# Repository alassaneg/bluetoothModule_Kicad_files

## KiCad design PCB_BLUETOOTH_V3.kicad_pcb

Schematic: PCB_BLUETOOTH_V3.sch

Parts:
C1, C9: 4,7uF; C_0805_2012Metric_Pad1.15x1.40mm_HandSolder; Manufacturer_Part_Number GRM21BR61H475KE51L; Farnell Part Number 2611942
C2, C3: 10uF; C_0805_2012Metric_Pad1.15x1.40mm_HandSolder; Manufacturer_Part_Number 08051A330JAT2A; Farnell Part Number 317603
C4, C7, C14, C15, C16, C17, C21, C22: 100nF; C_0603_1608Metric_Pad1.05x0.95mm_HandSolder; Manufacturer_Part_Number 06033D104KAT2A; Farnell Part Number 2332591
C8, C20: 10uF; C_0805_2012Metric_Pad1.15x1.40mm_HandSolder; Manufacturer_Part_Number C0805C106K3PACTU; Farnell Part Number 2491176
C11: 470nF; C_0603_1608Metric_Pad1.05x0.95mm_HandSolder; Manufacturer_Part_Number GRM033R60J474KE90D; Farnell Part Number 2990686
C12, C13, C19, C24, C27, C28, C30, C32: 1uF; C_0603_1608Metric_Pad1.05x0.95mm_HandSolder; Manufacturer_Part_Number 06033D105KAT2A; Farnell Part Number 1658868
C18, C26: 33pF; C_0805_2012Metric_Pad1.15x1.40mm_HandSolder; Manufacturer_Part_Number 08051A330JAT2A; Farnell Part Number 317603
C23, C25, C29, C31: 15pF; C_0805_2012Metric_Pad1.15x1.40mm_HandSolder; Manufacturer_Part_Number 08051A150JAT2A; Farnell Part Number 1658873
D1, D2, D3, D4, D9, D12, D13, D14: KPTR-3216SURCK; LED_0805_2012Metric_Pad1.15x1.40mm_HandSolder; Manufacturer_Part_Number KPTR-3216SURCK; Farnell Part Number 2099256
D5: DIODE; D_SOD-123; Manufacturer_Part_Number SBR1A40S1; Farnell Part Number 2061529
D6, D7: MAX40203AUK+T; SOT95P280X145-5N; Manufacturer_Part_Number MAX40203AUK+T; Mouser Part Number 700-MAX40203AUK+T
D8: ESD5B_ESD; D_SOD-323_HandSoldering; Manufacturer_Part_Number ESD5B5.0ST1G; Farnell Part Number 2317513
D11: KPT-1608EC; LED_0603_1608Metric_Pad1.05x0.95mm_HandSolder; Manufacturer_Part_Number KPTR-3216SURCK; Farnell Part Number 2099256
DS1: KCDA39-105; KCDA39105; Manufacturer_Part_Number KPT-1608EC; Mouser Part Number N/A
IC2: PIC18F46J50-I_PT; QFP80P1200X1200X120-44N; Manufacturer_Part_Number PIC18F46J50-I/PT; Mouser Part Number 579-PIC18F46J50-I/PT
IC3, IC4: SIP32431DR3-T1GE3; SOT65P210X110-6N; Manufacturer_Part_Number SIP32431DR3-T1GE3; Mouser Part Number 781-SIP32431DR3-GE3
IC6: MAX17263LETD+; SON40P300X300X80-15N; Manufacturer_Part_Number MAX17263LETD+; Mouser Part Number 700-MAX17263LETD+
IC7: WT32i-A-AI6; WT32I-A-AI6; Manufacturer_Part_Number WT32i-A-AI6; Mouser Part Number 603-WT32I-A-AI6
IC8: AD8476ARMZ; SOP65P490X110-8N; Manufacturer_Part_Number AD8476ARMZ; Mouser Part Number 584-AD8476ARMZ
J1: UART; PinSocket_1x04_P2.54mm_Vertical
J2: CL1308G; Manufacturer_Part_Number CL1308G; Farnell Part Number 2766190
J3: PJRAS1X2S01X; Mouser Part Number 502-PJRAS1X2S01X
J4: SP-3533-02; SP353302; Manufacturer_Part_Number SP-3533-02; Mouser Part Number 490-SP-3533-02
J5: 22-03-5035; SHDR3W70P0X250_1X3_990X490X590P; Manufacturer_Part_Number 22-03-5035; Mouser Part Number 538-22-03-5035
J6: ICSP_UC; PinSocket_1x05_P2.54mm_Vertical
J8: USB_B_Micro; DX4R005HJ5
J9: SPI_WT32i; PinSocket_1x06_P2.54mm_Vertical
JP1: Jumper_AUDIO_ROUTING; PinHeader_1x03_P2.54mm_Vertical; Manufacturer_Part_Number 22-28-4031; Farnell Part Number 3049527
JP2: Jumper_MONO_STEREO; PinHeader_1x03_P2.54mm_Vertical; Manufacturer_Part_Number 22-28-4031; Farnell Part Number 3049527
JP3: Jumper_NO_Small; PinHeader_1x02_P2.54mm_Vertical
JP4: Jumper_ICSP; PinHeader_1x02_P2.54mm_Vertical; Manufacturer_Part_Number 90120-0762; Farnell Part Number 9733302
JP5: JP_UART_RX; PinHeader_1x02_P2.54mm_Vertical; Manufacturer_Part_Number 90120-0762; Farnell Part Number 9733302
JP8: JP_UART_TX; PinHeader_1x02_P2.54mm_Vertical; Manufacturer_Part_Number 90120-0762; Farnell Part Number 9733302
L1, L4: 33nH; L_0805_2012Metric_Pad1.15x1.40mm_HandSolder; Manufacturer_Part_Number CE201210-33NJ; Farnell Part Number 2858904
L2, L3, L5, L6: 15nH; L_0603_1608Metric_Pad1.05x0.95mm_HandSolder; Manufacturer_Part_Number CE201210-15NJ; Farnell Part Number 2858903
Q1, Q2, Q3, Q4, Q5, Q6, Q7: 2SC4102FRAT106; RYU002N05T306; Manufacturer_Part_Number 2SC4102FRAT106
R1, R2: 1000kOhm; R_0805_2012Metric_Pad1.15x1.40mm_HandSolder; Manufacturer_Part_Number CRCW08050000Z0EA; Farnell Part Number 1469846
R5: 10M; R_0805_2012Metric_Pad1.15x1.40mm_HandSolder; Manufacturer_Part_Number CRCW080510M0FKEA; Farnell Part Number 1469858
R6, R7, R8, R9: 1.6kOhm; R_0805_2012Metric_Pad1.15x1.40mm_HandSolder; Manufacturer_Part_Number ERJ6ENF2150V; Farnell Part Number 2303478
R10, R14, R17: 2,2k; R_0805_2012Metric_Pad1.15x1.40mm_HandSolder; Manufacturer_Part_Number CRCW08052K20FKEA; Farnell Part Number 1469887
R11, R12, R13, R16: 7,5k; R_0805_2012Metric_Pad1.15x1.40mm_HandSolder; Manufacturer_Part_Number CRCW08057K50FKEA; Farnell Part Number 1653036
R15: 1.74kOhm; R_0805_2012Metric_Pad1.15x1.40mm_HandSolder; Manufacturer_Part_Number CRCW0805120RFKEA; Farnell Part Number 1652914
R18: 402ohm; L_0603_1608Metric_Pad1.05x0.95mm_HandSolder; Manufacturer_Part_Number ERA6AEB4020V; Farnell Part Number 1810462
R19, R39, R40: 5.1k; R_0805_2012Metric_Pad1.15x1.40mm_HandSolder; Manufacturer_Part_Number CRCW08055K00FKTA; Farnell Part Number 2616759
R20, R22, R24, R26, R27, R30, R31: 240k; R_0805_2012Metric_Pad1.15x1.40mm_HandSolder; Manufacturer_Part_Number ERJ6ENF4223V; Farnell Part Number 2303832
R21, R23, R25, R28, R29, R32, R33: 806ohm; R_0805_2012Metric_Pad1.15x1.40mm_HandSolder; Manufacturer_Part_Number ERJ6ENF6980V; Farnell Part Number 2303535
R34, R35, R36, R37: 10k; R_0805_2012Metric_Pad1.15x1.40mm_HandSolder; Manufacturer_Part_Number CPF-A-0805B10KE1; Farnell Part Number 2483951
R44, R45, R46, R47, R48, R49: 0ohm; R_0805_2012Metric_Pad1.15x1.40mm_HandSolder; Manufacturer_Part_Number CRCW08050000Z0EA; Farnell Part Number 1469846
R52: 1.74kOhm; R_0805_2012Metric_Pad1.15x1.40mm_HandSolder; Manufacturer_Part_Number ERA6AEB4020V; Farnell Part Number 1810462
R53, R54, R55: 1.74kOhm; R_0402_1005Metric; Manufacturer_Part_Number CRCW0402120RFKED; Farnell Part Number 2140682
S1: 450302014072; Manufacturer_Part_Number 450302014072; Mouser Part Number 710-450302014072
S2: PT65301; Manufacturer_Part_Number PT65301; Mouser Part Number 642-PT65301
TP1, TP4: 3V3; TestPoint_Pad_D1.0mm
TP2: GND; TestPoint_Pad_D1.0mm
TP3: Clock; TestPoint_Pad_D1.0mm
TP7: DIG1_7seg; TestPoint_Pad_D1.0mm
TP8: DIG2_7seg; TestPoint_Pad_D1.0mm
U1: REG113NA-3.3_3K; Texas_Instruments-DBV0005A-0-0-IPC_A; dropout voltage 250mV; output voltage 3.3V; mouser part number 595-REG113NA-3.3/3K; digikey description IC REG LINEAR 3.3V 400MA SOT23-5
U2: OPA1671IDCKT; SOT65P210X110-5N; Manufacturer_Part_Number OPA1671IDCKT; Mouser Part Number 595-OPA1671IDCKT

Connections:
3V3: C7.1, C8.2, C9.1, C12.1, C13.1, C16.1, C21.2, C22.2, D9.2 (A), D13.2 (A), IC2.7 (VDD), IC2.28 (VDD_1), IC3.4 (IN), IC4.4 (IN), IC7.1 (VREG_ENA), IC7.17 (VDD_IO), IC8.2 (+VS), J6.4, J9.1, R1.1, R19.1, R34.1, R35.1, R39.1, R40.1, S2.C1, S2.C2, TP1.1, U1.5 (VOUT), U2.5 (V+)
/DIFF1+: L2.2, R10.1, R11.2
/DIFF1-: L3.2, R10.2, R13.2
/DIFF2+: C19.2, C23.1, L2.1
/DIFF2-: C24.2, C25.1, L3.1
/DIFF3+: C19.1, R44.2
/DIFF3-: C24.1, R46.2
AUDIO_DIFF_N: IC8.5 (-OUT), R13.1
AUDIO_DIFF_P: IC8.4 (+OUT), R11.1
AUDIO_IN_N_LEFT_N: IC7.45 (AUDIO_IN_N_LEFT), R46.1, R47.1
AUDIO_IN_N_RIGHT: C32.2, IC7.42 (AUDIO_IN_N_RIGHT_N)
AUDIO_IN_P_LEFT_P: IC7.44 (AUDIO_IN_P_LEFT), R44.1, R45.1
AUDIO_IN_P_RIGHT: C30.1, IC7.41 (AUDIO_IN_P_RIGHT_P)
AUDIO_MONO_STEREO: IC2.2 (RD4/PMD4/RP21), JP2.2 (C)
AUDIO_OUT_N_LEFT: IC7.49 (AUDIO_OUT_N_LEFT)
AUDIO_OUT_N_RIGHT: IC7.46 (AUDIO_OUT_N_RIGHT)
AUDIO_OUT_P_LEFT: C18.1, IC7.50 (AUDIO_OUT_P_LEFT), L1.1
AUDIO_OUT_P_LEFT_MONO: J3.T2, L1.2, R49.1
AUDIO_OUT_P_RIGHT: C26.1, IC7.47 (AUDIO_OUT_P_RIGHT), L4.1
AUDIO_ROUTING: IC2.3 (RD5/PMD5/RP22), JP1.2 (C)
AUDIO_SINGLE_ENDED_MONO: IC8.8 (INP), U2.1 (OUT), U2.4 (-IN)
A_7SEG: IC2.26 (RE1/AN6/PMWR), R20.2
BAT_TH: IC6.1 (TH), J5.2
B_7SEG: IC2.19 (RA0/AN0/C1INA/ULPWU/PMA6/RP0), R22.2
C_7SEG: IC2.21 (RA2/AN2/VREF-/CVREF-/C2INB), R24.2
DIG1: C15.1, DS1.10 (COM_A_DIG1), IC3.1 (OUT)
DIG1_7SEG: IC2.20 (RA1/AN1/C2INA/PMA7/RP1), IC3.3 (ON/OFF), TP7.1
DIG2: C14.1, DS1.5 (COMA_DIG2), IC4.1 (OUT)
DIG2_7SEG: IC2.24 (RA5/AN4/~SS1~/HLVDIN/RCV/RP2), IC4.3 (ON/OFF), TP8.1
D_7SEG: IC2.25 (RE0/AN5/PMRD), R27.2
E_7SEG: IC2.22 (RA3/AN3/VREF+/C1INB), R31.2
F_7SEG: IC2.27 (RE2/AN7/PMCS), R26.2
GND: C1.2, C3.1, C4.2, C7.2, C8.1, C9.2, C11.2, C12.2, C13.2, C14.2, C15.2, C16.2, C17.2, C18.2, C20.1, C21.1, C22.1, C23.2, C25.2, C26.2, C27.1, C29.2, C31.2, C32.1, D6.2 (GND), D7.2 (GND), D8.2 (A), D11.1 (K), D12.1 (K), D14.1 (K), IC2.6 (VSS), IC2.29 (VSS_1), IC3.2 (GND_1), IC3.5 (GND_2), IC4.2 (GND_1), IC4.5 (GND_2), IC6.8 (GND), IC6.9 (CSPL), IC6.12 (ALRT), IC6.15 (EP), IC7.2 (GND_1), IC7.3 (GND_2), IC7.4 (GND_3), IC7.18 (GND_4), IC7.21 (UART_NCTS), IC7.31 (GND_5), IC7.39 (GND_6), IC7.43 (GND_7), IC7.48 (GND_8), IC8.1 (INN), IC8.7 (-VS), J1.2, J2.3, J3.S1, J4.3 (SLEEVE), J5.3, J6.3, J8.5 (GND), J8.6 (Shield), J9.6, Q1.1, Q2.1, Q3.1, Q4.1, Q5.1, Q6.1, Q7.1, R2.2, R14.2, R17.2, R36.2, R37.2, R52.2, TP2.1, U1.2 (GND), U2.2 (V-)
G_7SEG: IC2.8 (RB0/AN12/INT0/RP3), R30.2
JACK_IN: C2.2, R48.1
MCLR: IC2.18 (~MCLR), JP4.1, R18.2, R19.2
unnamed: C1.1, D6.5 (OUT), S1.2 (NO), U1.1 (VIN), U1.3 (Enable)
unnamed: C2.1, C3.2, R1.2, R2.1, U2.3 (+IN)
unnamed: C11.1, IC6.11 (REG)
unnamed: C17.1, JP4.2
unnamed: C20.2, IC2.23 (VDDCORE/VCAP)
unnamed: C27.2, R47.2
unnamed: C28.1, R45.2
unnamed: C28.2, C29.1, L5.1
unnamed: C30.2, C31.1, L6.1
unnamed: D1.1 (K), D2.1 (K), D3.1 (K), IC6.2 (L1), R7.2
unnamed: D1.2 (A), R6.2
unnamed: D2.2 (A), R8.2
unnamed: D3.2 (A), R9.2
unnamed: D4.1 (K), IC6.3 (L2), R6.1
unnamed: D4.2 (A), R7.1
unnamed: D5.2 (A), IC7.19 (RESET)
unnamed: D9.1 (K), R15.1
unnamed: D11.2 (A), R55.2
unnamed: D12.2 (A), R53.1
unnamed: D13.1 (K), R52.1
unnamed: D14.2 (A), R54.1
unnamed: IC2.1 (RC7/PMA4/RX1/DT1/SDO1/RP18), JP8.2
unnamed: IC2.31 (OSC2/CLKO/RA6), TP3.1
unnamed: IC2.42 (RC4/D-/VM), R55.1
unnamed: IC2.44 (RC6/PMA5/TX1/CK1/RP17), JP5.1
unnamed: IC6.4 (L3), R8.1
unnamed: IC6.5 (L4), R9.1
unnamed: IC7.22 (PIO8), R53.2
unnamed: IC7.23 (PIO7), R54.2
unnamed: IC7.36 (LED0), R15.2
unnamed: J2.1, R48.2, R49.2
unnamed: J3.T1, L4.2
unnamed: J4.1 (TIP), R12.1
unnamed: J4.2 (RING), R16.1
unnamed: J6.5, R18.1
unnamed: JP1.1 (A), R36.1
unnamed: JP1.3 (B), R34.2
unnamed: JP2.1 (A), R37.1
unnamed: JP2.3 (B), R35.2
unnamed: L5.2, R12.2, R14.1
unnamed: L6.2, R16.2, R17.1
unnamed: Q1.2, R20.1
unnamed: Q1.3, R21.2
unnamed: Q2.2, R22.1
unnamed: Q2.3, R23.2
unnamed: Q3.2, R24.1
unnamed: Q3.3, R25.2
unnamed: Q4.2, R26.1
unnamed: Q4.3, R28.2
unnamed: Q5.2, R27.1
unnamed: Q5.3, R29.2
unnamed: Q6.2, R30.1
unnamed: Q6.3, R32.2
unnamed: Q7.2, R31.1
unnamed: Q7.3, R33.2
PGC: IC2.16 (RB6/KBI2/PGC/RP9), J6.1, S2.4
PGD: IC2.17 (RB7/KBI3/PGD/RP10), J6.2, S2.8
RESET_WT32i: D5.1 (K), IC2.4 (RD6/PMD6/RP23)
ROTARY_IN1: IC2.14 (RB4/PMA1/KBI0/SCK1/SCL1/RP7), S2.1
ROTARY_IN2: IC2.15 (RB5/PMA0/KBI1/SDI1/SDA1/RP8), S2.2
SCL: IC2.38 (RD0/PMD0/SCL2), IC6.14 (SCL), R40.2
SDA: IC2.39 (RD1/PMD1/SDA2), IC6.13 (SDA), R39.2
SEG_A: DS1.3 (K_A), R21.1
SEG_B: DS1.9 (K_B), R23.1
SEG_C: DS1.8 (K_C), R25.1
SEG_D: DS1.6 (K_D), R29.1
SEG_E: DS1.7 (K_E), R33.1
SEG_F: DS1.4 (K_F), R28.1
SEG_G: DS1.1 (K_G), R32.1
SPI_CLK: IC7.33 (SPI_CLK), J9.4
SPI_CS: IC7.32 (SPI_NCSB), J9.5
SPI_MISO: IC7.34 (SPI_MISO), J9.3
SPI_MOSI: IC7.35 (SPI_MOSI), J9.2
UART_RX: IC7.15 (UART_RXD), J1.3, JP5.2
UART_RX_2: IC2.40 (RD2/PMD2/RP19), JP3.1
UART_TX: IC7.16 (UART_TXD), J1.4, JP8.1
UART_TX_2: IC2.41 (RD3/PMD3/RP20), JP3.2
VBAT_IN: C4.1, IC6.6 (BATT), IC6.7 (CSN), IC7.37 (VDD_BAT), J5.1, R5.2, TP4.1
VBAT_OUT: D7.1 (VDD), D7.3 (EN), IC6.10 (CELLX/CSPH), R5.1
VUSB: D6.1 (VDD), D6.3 (EN), D8.1 (K), IC7.38 (VDD_CHG), J8.1 (VBUS)
V_LDO: D7.5 (OUT), S1.1 (COM)

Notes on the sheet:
MICROCONTROLEUR revoir interruption codeur(multiple interruptions) voir reset wt32i lors reprog led debug
AFFICHEUR 7 SEGMENTS
ALIMENTATION METTRE CONNECTEURS ALIM
WT32i Prévoir capa de liaison sortie vers ampli, et molex (plus tard)
AUDIO Changer RCA et capa liaison sortie
LDO
Jauge de batterie
SI SPI n'almenter que le module WT32i
R41 = résistance de pull down (donc à relier à GND) pour reset MCU lors de test UART
A2DP_IN/OUT MONO/STEREO
Peut être en entrée ou en sortie. Mettre interrupteur pour sélectionner entrèe ou sortie(uniquement pour mono avec guitare)
AUDIO OUT
AUDIO IN
A2DP_IN
A2DP_OUT
MONO
STEREO
Interrupteur(sert uniquement pour la batterie) SI USB branché, bypass de l'interrupteur Remplacer capa découplage reg113na
Si sortie = 1 => Interrupteur fermé (et éventuellement USB branché)(réveil le uc)/ USB débranché et interrupteur ouvert = UC non alimenté Si sortie = 0 => USB branché et interrupteur ouvert (réveil UC, envoie commande SPI, on endort l'UC)
Diode POWER ON (rouge)
LED indiquant si connecté(set control CD)
Battery low led
CONNECTER TH SUR BAT SI NON UTILISE
LED DEBUG ROUGE
- Revoir power on/off VREG_ENA
LED VERTES
LED ROUGES

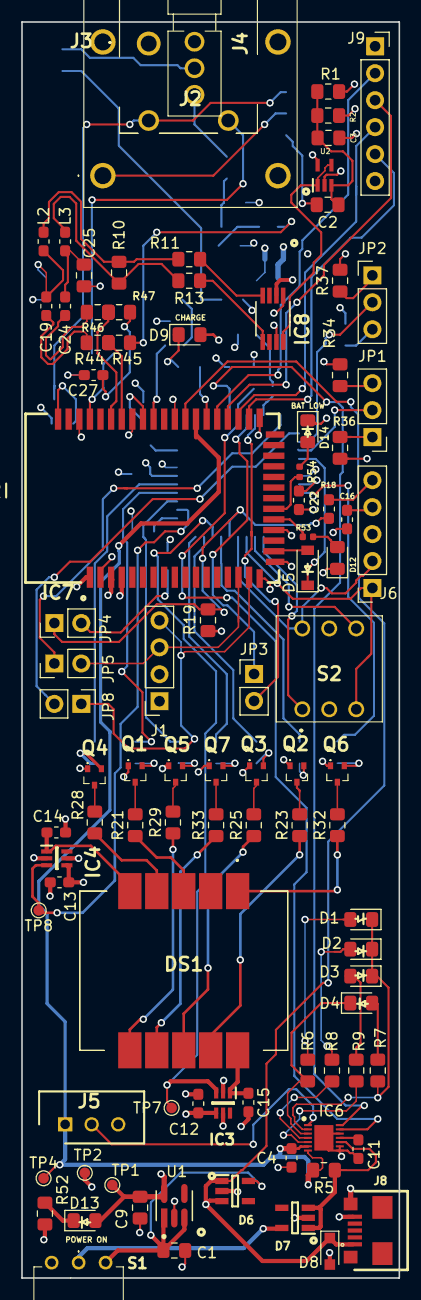
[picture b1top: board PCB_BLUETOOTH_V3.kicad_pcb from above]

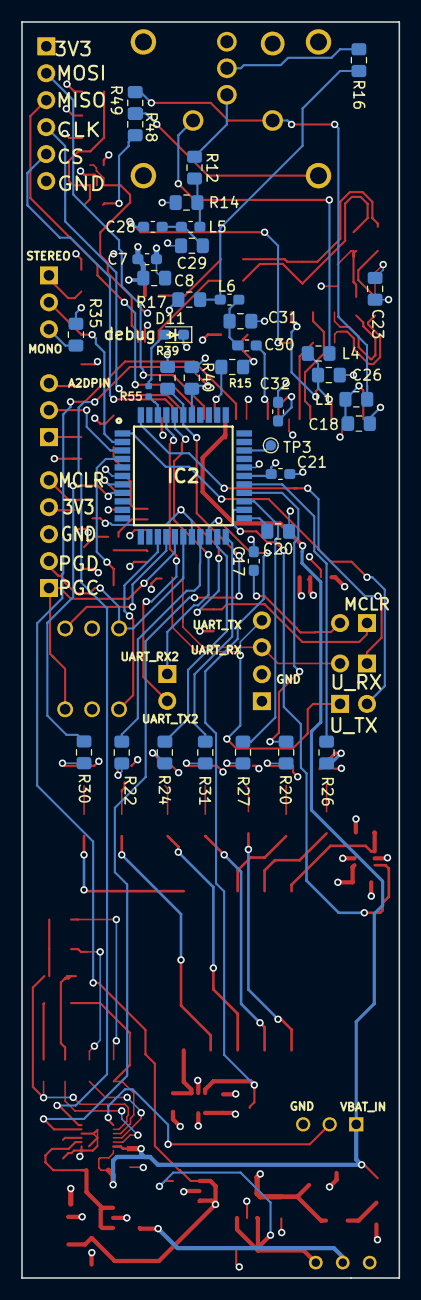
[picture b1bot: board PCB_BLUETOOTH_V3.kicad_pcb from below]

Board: 4 copper layers, 35.6 x 118.4 mm, 133 parts (38 on the bottom side), 115 nets.

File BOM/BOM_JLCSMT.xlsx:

Comment | Designator | Footprint | LCSC Part #（optional）
4,7uF | C1, C9 | Capacitor_SMD:C_0805_2012Metric_Pad1.15x1.40mm_HandSolder | C1779
100nF | C4, C7, C14, C15, C16, C17,C21, C22 | Capacitor_SMD:C_0603_1608Metric_Pad1.05x0.95mm_HandSolder | C14663
470nF | C11 | Capacitor_SMD:C_0603_1608Metric_Pad1.05x0.95mm_HandSolder | C1623
1uF | C12, C13, C19, C24, C27, C28, C30, C32 | Capacitor_SMD:C_0603_1608Metric_Pad1.05x0.95mm_HandSolder | C29936
33pF | C18, C26 | Capacitor_SMD:C_0805_2012Metric_Pad1.15x1.40mm_HandSolder | C1663 | not x7r
10uF | C2, C3, C8, C20 | Capacitor_SMD:C_0805_2012Metric_Pad1.15x1.40mm_HandSolder | C440198
15pF | C23, C25, C29, C31 | Capacitor_SMD:C_0805_2012Metric_Pad1.15x1.40mm_HandSolder | C1794 | not x7r
LED RED | D9, D12, D13, D14 | LED_SMD:LED_0805_2012Metric_Pad1.15x1.40mm_HandSolder | C84256
LED GREEN | D1, D2, D3, D4 | LED_SMD:LED_0805_2012Metric_Pad1.15x1.40mm_HandSolder | C63855
DIODE | D5 | Diode_SMD:D_SOD-123 | C132115
MAX40203AUK+T | D6, D7 | MAX40203AUK+T:SOT95P280X145-5N
ESD5B_ESD | D8 | Diode_SMD:D_SOD-323_HandSoldering | C38388
LED RED | D11 | LED_SMD:LED_0603_1608Metric_Pad1.05x0.95mm_HandSolder | C2286
KCDA39-105 | DS1 | KCDA39-105:KCDA39105
PIC18F46J50-I_PT | IC2 | PIC18F46J50-I_PT:QFP80P1200X1200X120-44N
SIP32431DR3-T1GE3 | IC3,IC4 | SIP32431DR3-T1GE3:SOT65P210X110-6N
MAX17263LETD+ | IC6 | MAX17263LETD+V:SON40P300X300X80-15N
WT32i-A-AI6 | IC7 | WT32i-A-AI6:WT32I-A-AI6
AD8476ARMZ | IC8 | AD8476ARMZ:SOP65P490X110-8N
33nH | L1, L4 | Inductor_SMD:L_0805_2012Metric_Pad1.15x1.40mm_HandSolder | C98993
15nH | L2, L3, L5, L6 | Inductor_SMD:L_0603_1608Metric_Pad1.05x0.95mm_HandSolder | C23651
2SC4102FRAT106 | Q1, Q2, Q3, Q4, Q5, Q6, Q7 | RYU002N05T306
1000kOhm | R1, R2 | Resistor_SMD:R_0805_2012Metric_Pad1.15x1.40mm_HandSolder | C17514
10M | R5 | Resistor_SMD:R_0805_2012Metric_Pad1.15x1.40mm_HandSolder | C26108
1.6kOhm | R6, R7, R8, R9 | Resistor_SMD:R_0805_2012Metric_Pad1.15x1.40mm_HandSolder | C17394
2,2k | R10 , R14, R17 | Resistor_SMD:R_0805_2012Metric_Pad1.15x1.40mm_HandSolder | C17520
7,5k | R11, R12, R13, R16 | Resistor_SMD:R_0805_2012Metric_Pad1.15x1.40mm_HandSolder | C17807
1.74kOhm | R15, R52,R53, R54, R55 | Resistor_SMD:R_0805_2012Metric_Pad1.15x1.40mm_HandSolder | C17395
402ohm | R18 | Inductor_SMD:L_0603_1608Metric_Pad1.05x0.95mm_HandSolder | C23049
5.1k | R19, R39, R40 | Resistor_SMD:R_0805_2012Metric_Pad1.15x1.40mm_HandSolder | C27834
240k | R20, R22, R24, R26, R27, R30, R31 | Resistor_SMD:R_0805_2012Metric_Pad1.15x1.40mm_HandSolder | C25824
806ohm | R21, R23, R25, R28, R29, R32, R33 | Resistor_SMD:R_0805_2012Metric_Pad1.15x1.40mm_HandSolder | C17834
10k | R34, R35, R36, R37 | Resistor_SMD:R_0805_2012Metric_Pad1.15x1.40mm_HandSolder | C17414
0ohm | R3, R44, R45, R46, R47, R48, R49 | Resistor_SMD:R_0805_2012Metric_Pad1.15x1.40mm_HandSolder
REG113NA-3.3_3K | U1 | REG113NA:Texas_Instruments-DBV0005A-0-0-IPC_A
OPA1671IDCKT | U2 | OPA1671IDCKT:SOT65P210X110-5N

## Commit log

2021-03-30 premier depot
